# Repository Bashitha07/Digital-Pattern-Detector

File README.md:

# Digital Pattern Detector (`0011`)

**IE3004 – Digital Systems Design Assignment**  
**Sri Lanka Institute of Information Technology (SLIIT)**  
**B.Sc. (Hons) in Computer Systems Engineering**  
**Group 02**

## Project Overview

This project presents the hardware design, simulation, and PCB layout of a synchronous digital pattern detection system built with 74HC-series CMOS logic ICs.

The system:

1. Generates a pseudo-random 4-bit sequence using a linear feedback shift register (LFSR).
2. Loads each 4-bit word into a parallel-in, serial-out (PISO) shift register.
3. Transmits the word least-significant bit first.
4. Detects the overlapping binary pattern `0011` using a four-state Mealy finite-state machine (FSM).

The design was simulated in Proteus Design Suite and captured as a two-layer, through-hole PCB in KiCad.

## System Architecture

```text
+-------------------+       P3..P0       +-------------------+       X = Q0       +-------------------+
| 4-bit LFSR        | ------------------> | 4-bit PISO       | ------------------> | Mealy FSM         |
| pseudo-random     |                     | shift register   |                     | `0011` detector  |
+-------------------+                     +-------------------+                     +-------------------+
        ^                                          ^                                      |
        |                                          |                                      v
   [SW1 seed]                                 [LOAD control]                         Z (output)
                                             Common rising-edge CLK
```

All three subsystems use the same rising-edge clock.

## 1. 4-Bit LFSR

A maximal-length 4-bit LFSR cycles through all `2^4 - 1 = 15` non-zero states before repeating. The all-zero state is excluded because it would lock the register at zero.

The active-low asynchronous initialization input, controlled by push-button `SW1` and a `10 kΩ` pull-up resistor, loads the seed word:

```text
G3 G2 G1 G0 = 0001
```

The next-state equations are:

```text
Q3+ = Q2
Q2+ = Q1
Q1+ = Q0
Q0+ = Q3 XOR Q2
```

## 2. 4-Bit PISO Shift Register

The PISO register captures the LFSR output in parallel when `LOAD = 0`. When `LOAD = 1`, it shifts one bit toward `Q0` on each rising clock edge.

For `L = LOAD`, the D-input equations are:

```text
D3 = P3 · L'
D2 = Q3 · L + P2 · L'
D1 = Q2 · L + P1 · L'
D0 = Q1 · L + P0 · L'
```

The serial output is:

```text
X = Q0
```

Because transmission is least-significant bit first, a parallel word of `1100` produces the serial sequence:

```text
0 → 0 → 1 → 1
```

This sequence is the target pattern detected by the FSM.

## 3. Overlapping Mealy FSM Detector

The detector identifies `0011` using a four-state overlapping Mealy FSM. A Mealy machine generates its output from both the current state and the current input, allowing the detection pulse to occur during the clock cycle in which the final `1` arrives.

### State Encoding

| State | Encoding | Meaning |
| :--- | :---: | :--- |
| A | `00` | No useful prefix matched |
| B | `01` | Prefix `0` matched |
| C | `11` | Prefix `00` matched |
| D | `10` | Prefix `001` matched |

### Excitation and Output Equations

```text
D1 = Q0 · X' + Q1 · Q0
D0 = X'
Z  = Q1 · Q0' · X
```

The output `Z` is HIGH when the FSM is in state D and the current serial input `X` is `1`, indicating that `0011` has been detected.

### Self-Synchronization

Two consecutive `1` inputs drive the FSM to state A (`00`) from any state. This provides a practical way to place the detector in a known state without a dedicated FSM reset line.

## Integrated Circuit Allocation

| IC | Function | Packages Used | Utilization |
| :--- | :--- | :---: | :--- |
| `74HC74` | Dual D-type positive-edge flip-flop | 5 | 10 of 10 flip-flops |
| `74HC08` | Quad 2-input AND gate | 3 | 11 of 12 gates |
| `74HC32` | Quad 2-input OR gate | 1 | 4 of 4 gates |
| `74HC04` | Hex inverter | 1 | 3 of 6 inverters |
| `74HC86` | Quad 2-input XOR gate | 1 | 1 of 4 gates |

### Additional Components

- `1 × 10 kΩ` pull-up resistor
- `9 × 330 Ω` LED current-limiting resistors
- `9 ×` indicator LEDs (`D1–D9`)
- `1 ×` tactile push-button (`SW1`)
- `2 ×` 2-pin header connectors (`J1`, `J2`)

## Repository Contents

| Directory/File | Description |
| :--- | :--- |
| [`KiCad Files/`](KiCad%20Files/) | KiCad schematic, PCB layout, and project design files |
| [`Proteus/`](Proteus/) | Proteus simulation project and generated simulation files |
| [`Photos/`](Photos/) | PCB renders, board-layer views, schematics, and waveform captures |
| [`Report/`](Report/) | Technical reports and assignment documentation |
| [`README.md`](README.md) | Project overview and design documentation |

## Testing and Verification

### T1 – Seed Initialization

Stop the clock, press and release `SW1`, and verify that the LFSR is initialized to `0001`.

### T2 – LFSR Period

Apply 15 clock pulses and verify that all 15 non-zero states occur before the sequence returns to `0001`.

### T5 – FSM Synchronization

Apply two consecutive serial `1` inputs and verify that the FSM reaches state A (`00`).

### T6/T7 – Pattern Detection

1. Set `LOAD = 0` and apply one rising clock edge to load the selected LFSR word into the PISO register.
2. Set `LOAD = 1` and apply four rising clock edges.
3. For the loaded word `1100`, verify the serial sequence `0 → 0 → 1 → 1`.
4. Verify that `Z` pulses HIGH during the fourth transmitted bit, when the FSM detects the complete `0011` pattern.

## Design Files

- **KiCad:** [`KiCad Files/KiCad_Y3S1.kicad_sch`](KiCad%20Files/KiCad_Y3S1.kicad_sch) and [`KiCad Files/KiCad_Y3S1.kicad_pcb`](KiCad%20Files/KiCad_Y3S1.kicad_pcb)
- **Proteus:** [`Proteus/DSD_Final_Schematic.pdsprj`](Proteus/DSD_Final_Schematic.pdsprj)
- **Reports:** [`Report/`](Report/)

## Group Members

| Student ID | Name |
| :--- | :--- |
| `IT24103485` | Sellapperuma B.A. |
| `IT24100888` | L P Jayasinghe |
| `IT24610799` | Kalpage M.L.P. |

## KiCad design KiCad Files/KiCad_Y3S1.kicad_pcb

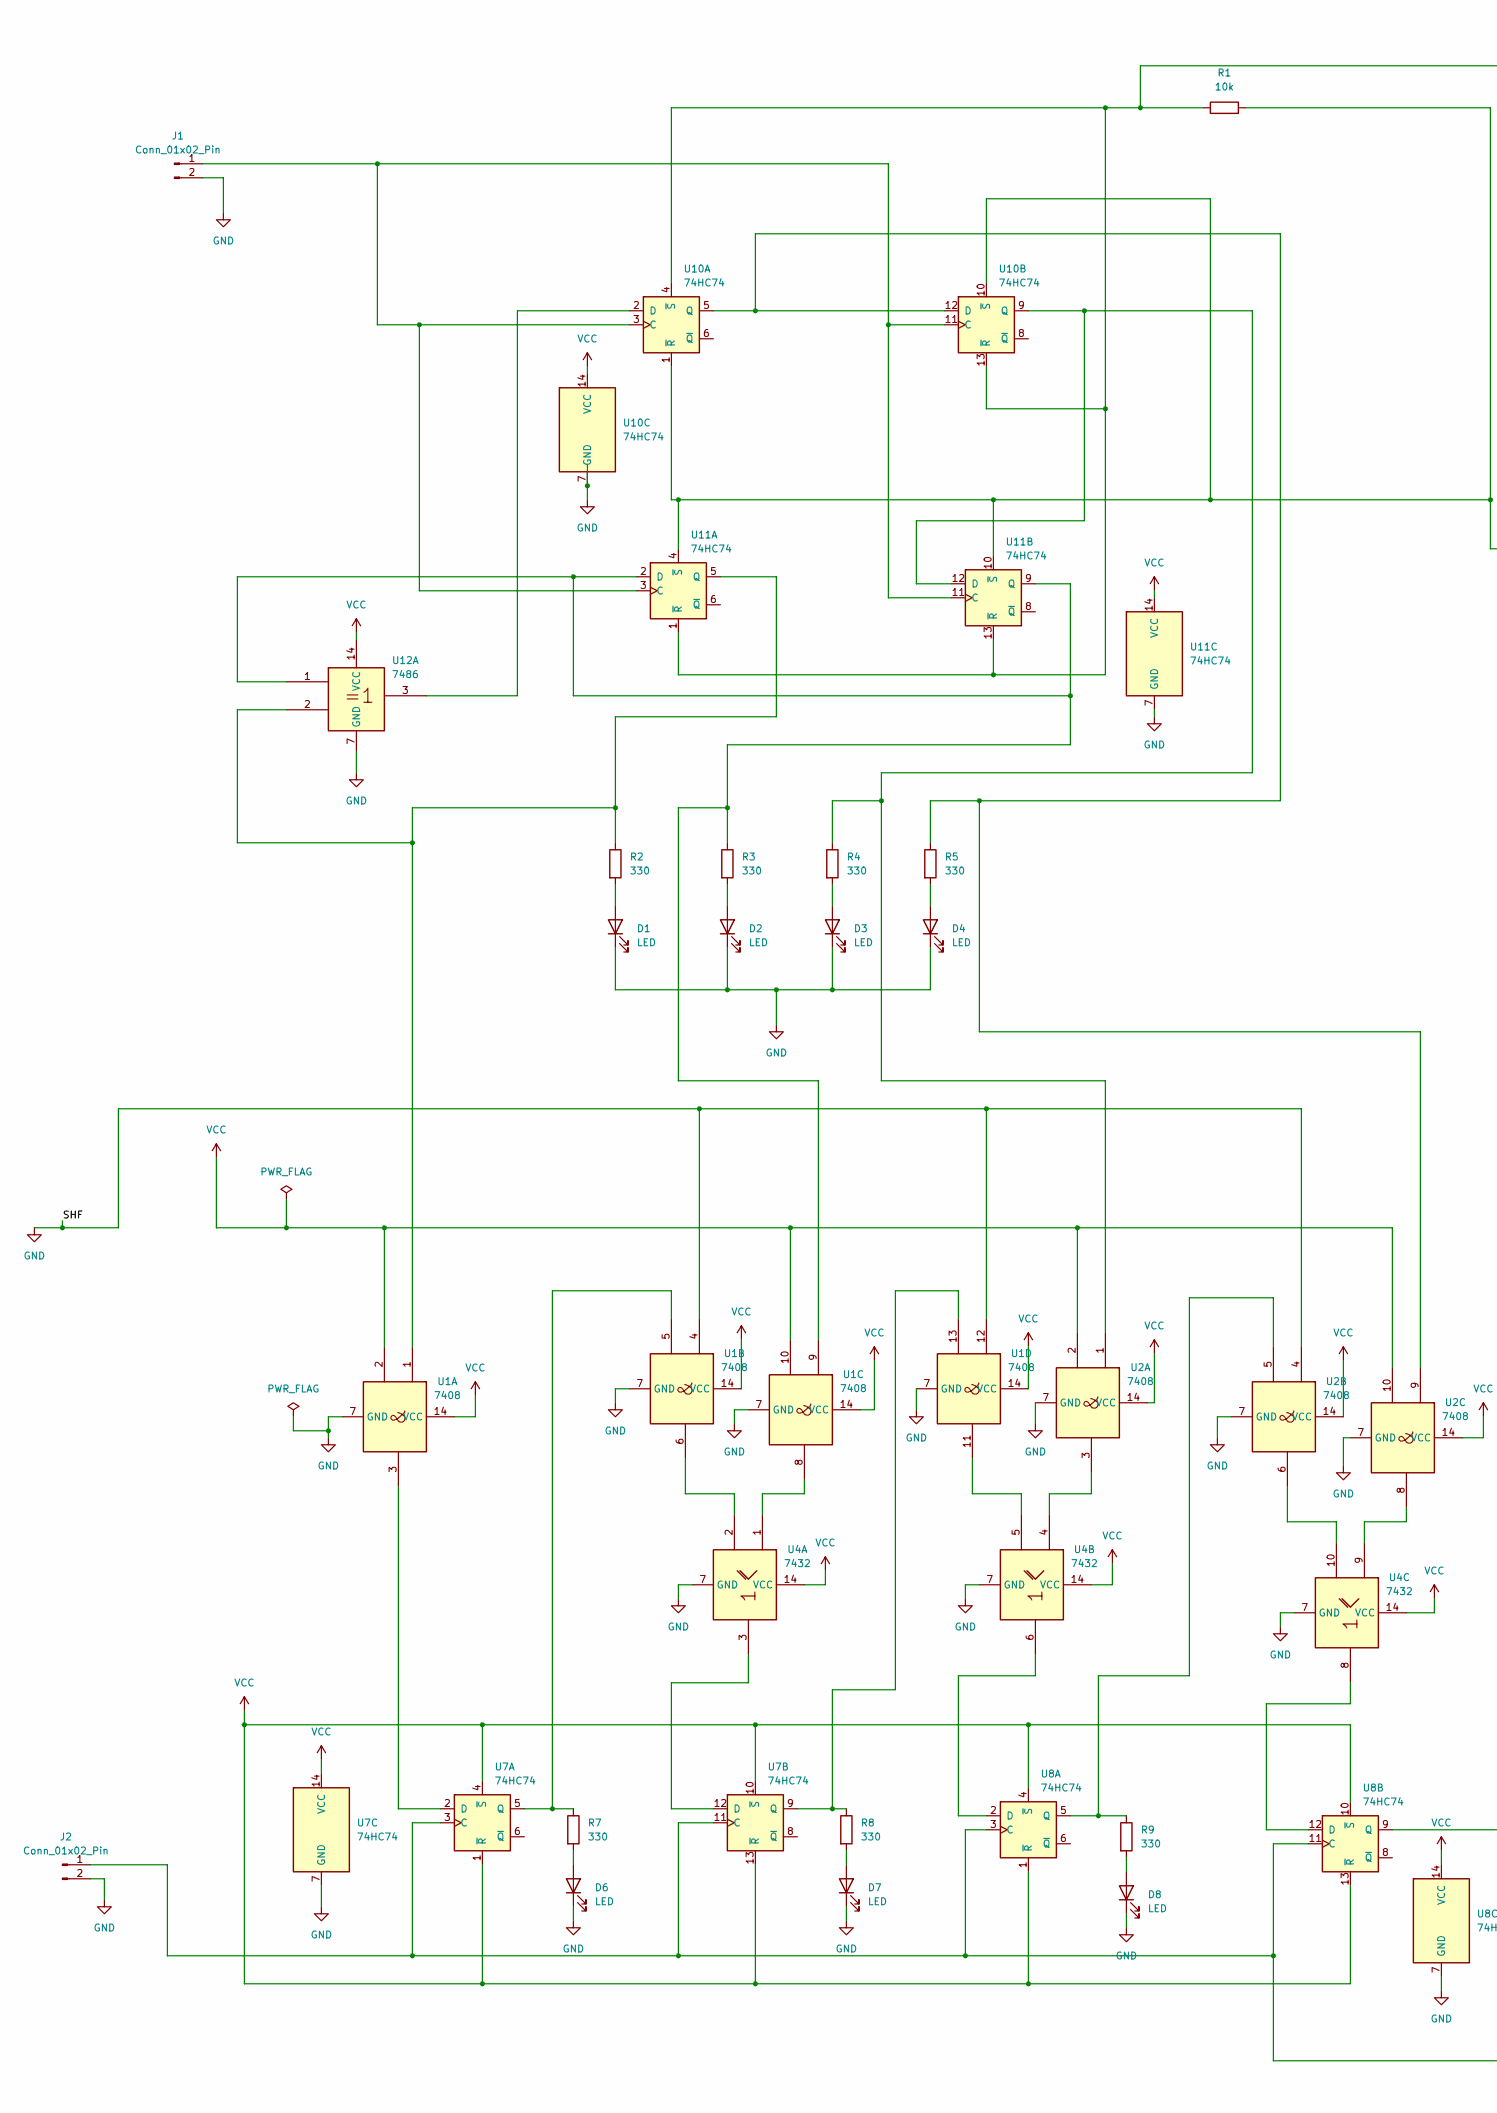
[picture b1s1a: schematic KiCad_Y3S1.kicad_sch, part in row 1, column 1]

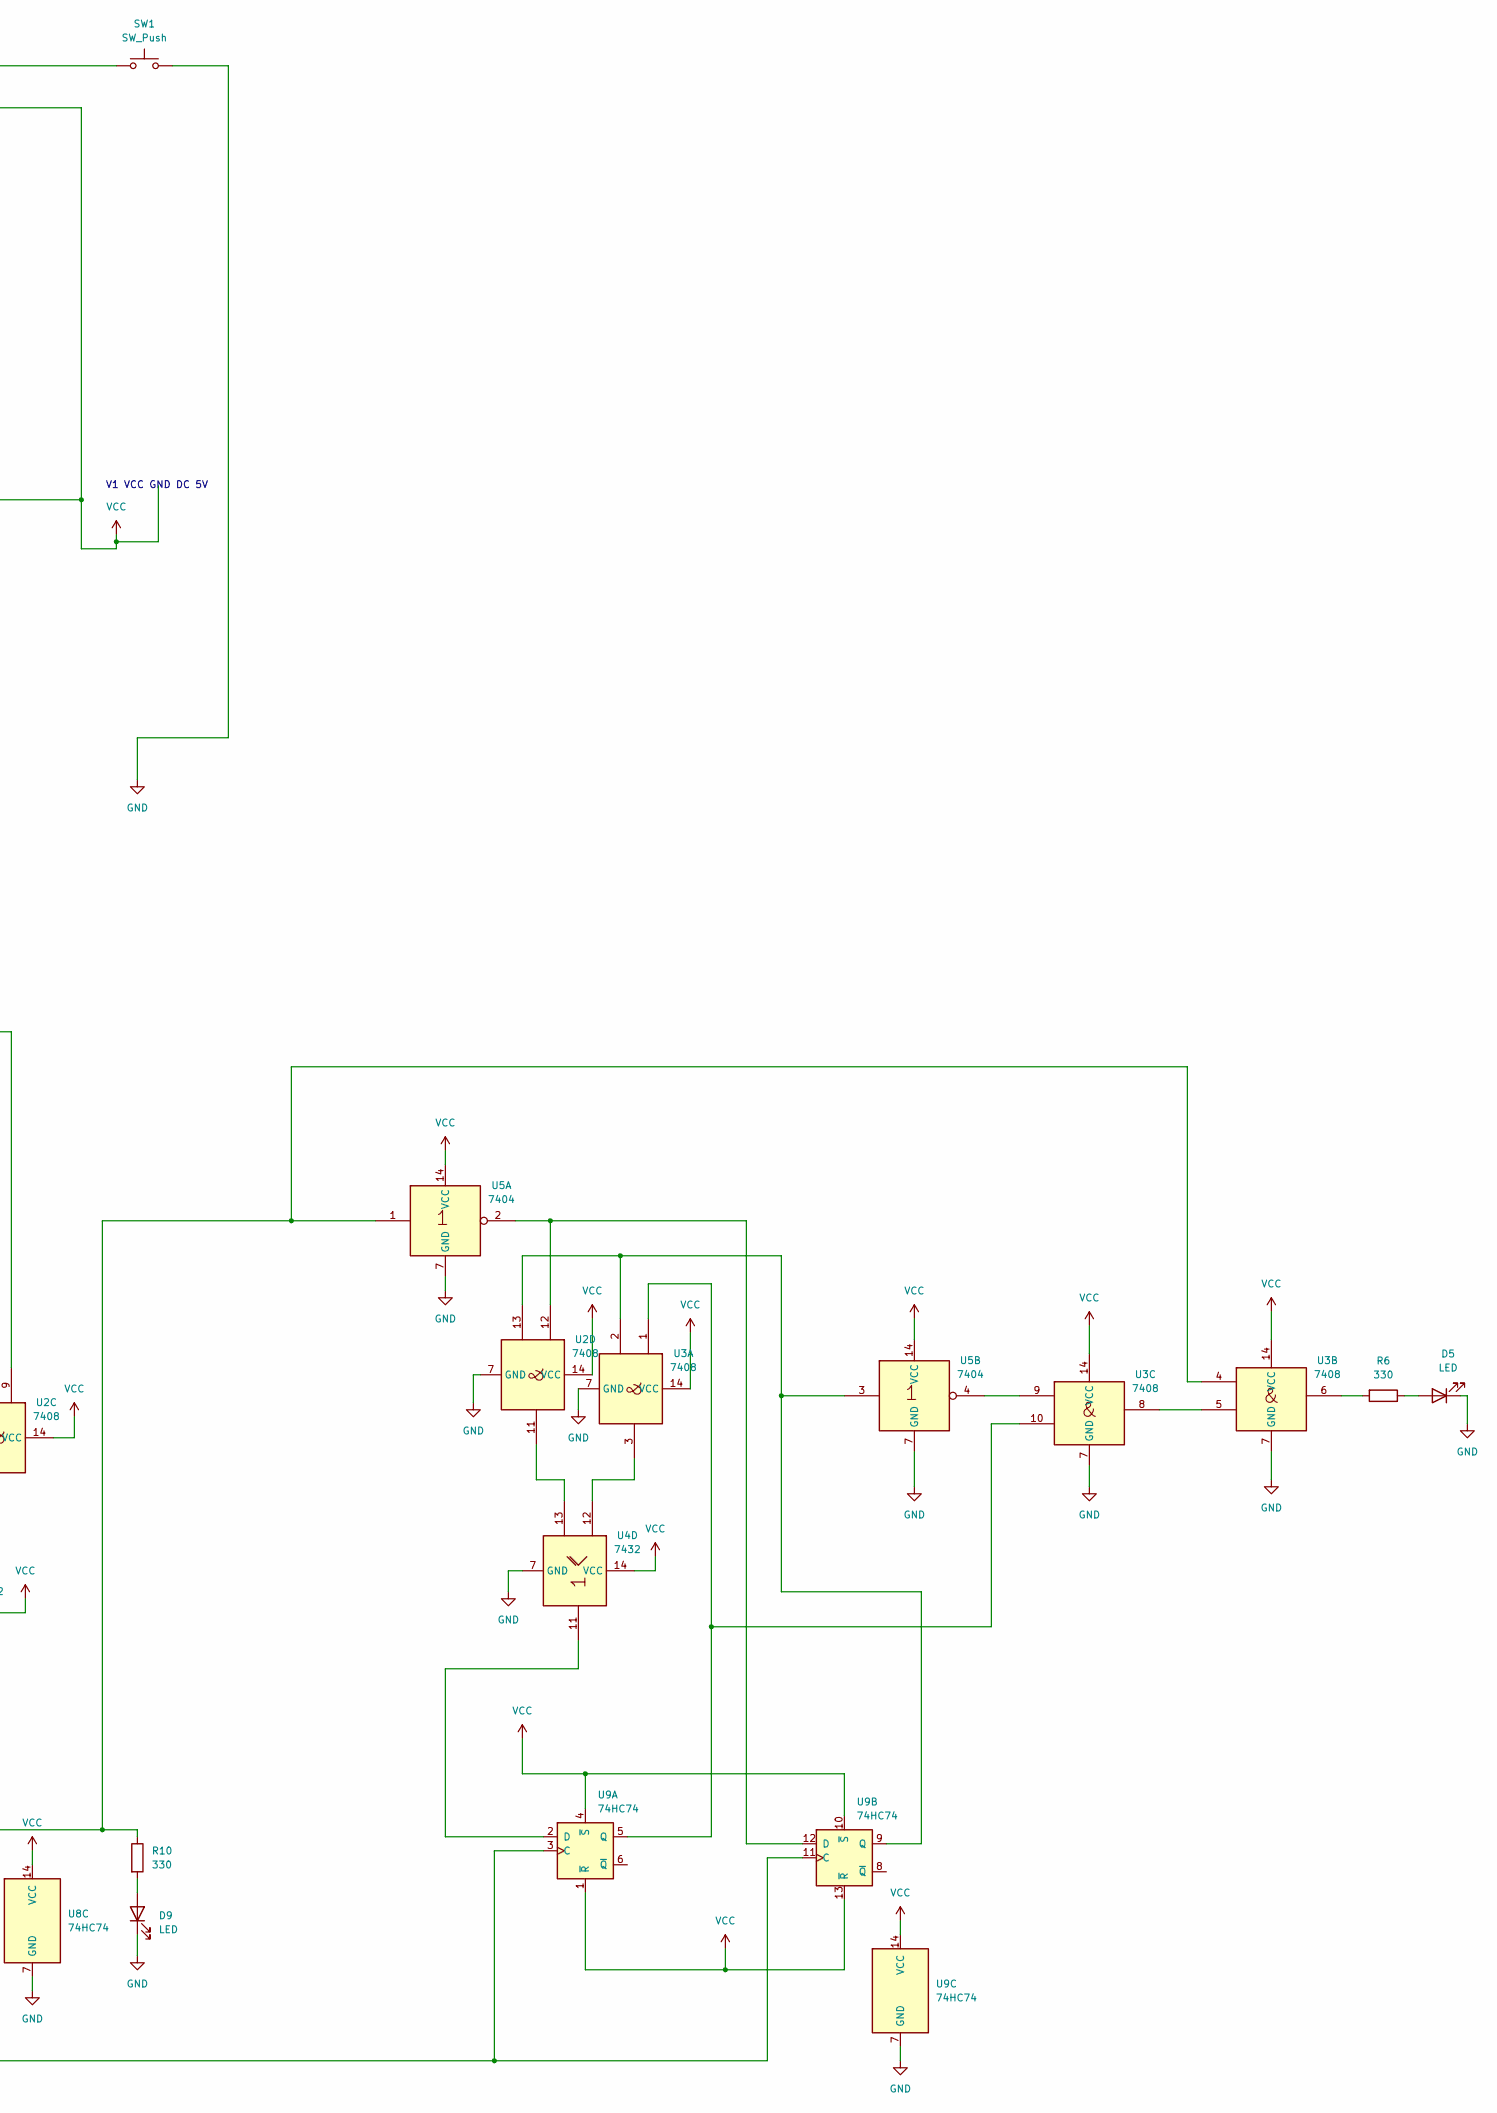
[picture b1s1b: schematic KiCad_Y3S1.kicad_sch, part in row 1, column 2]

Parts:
D1, D2, D3, D4, D5, D6, D7, D8, D9: LED; LED_D5.0mm
J1, J2: Conn_01x02_Pin; PinHeader_1x02_P2.54mm_Vertical
R1: 10k; R_Axial_DIN0207_L6.3mm_D2.5mm_P10.16mm_Horizontal
R2, R3, R4, R5, R6, R7, R8, R9, R10: 330; R_Axial_DIN0207_L6.3mm_D2.5mm_P10.16mm_Horizontal
SW1: SW_Push; SW_PUSH_6mm
U1, U2, U3: 7408; DIP-14_W7.62mm
U4: 7432; DIP-14_W7.62mm
U5: 7404; DIP-14_W7.62mm
U7, U8, U9, U10, U11: 74HC74; DIP-14_W7.62mm
U12: 7486; DIP-14_W7.62mm

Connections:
GND: D1.1 (K), D2.1 (K), D3.1 (K), D4.1 (K), D5.1 (K), D6.1 (K), D7.1 (K), D8.1 (K), D9.1 (K), J1.2, J2.2, SW1.2, U1.4, U1.7 (GND), U1.12, U2.4, U2.7 (GND), U3.7 (GND), U4.7 (GND), U5.7 (GND), U7.7 (GND), U8.7 (GND), U9.7 (GND), U10.7 (GND), U11.7 (GND), U12.7 (GND)
unnamed: D1.2 (A), R2.2
unnamed: D2.2 (A), R3.2
unnamed: D3.2 (A), R4.2
unnamed: D4.2 (A), R5.2
unnamed: D5.2 (A), R6.1
unnamed: D6.2 (A), R7.2
unnamed: D7.2 (A), R8.2
unnamed: D8.2 (A), R9.2
unnamed: D9.2 (A), R10.2
unnamed: J1.1, U10.3 (C), U10.11 (C), U11.3 (C), U11.11 (C)
unnamed: J2.1, U7.3 (C), U7.11 (C), U8.3 (C), U8.11 (C), U9.3 (C), U9.11 (C)
unnamed: R6.2, U3.6
unnamed: U1.6, U4.2
unnamed: U1.8, U4.1
unnamed: U1.11, U4.5
unnamed: U2.3, U4.4
unnamed: U2.6, U4.10
unnamed: U2.8, U4.9
unnamed: U2.11, U4.13
unnamed: U3.3, U4.12
unnamed: U3.5, U3.8
unnamed: U3.9, U5.4
unnamed: U1.3, U7.2 (D)
unnamed: R7.1, U1.5, U7.5 (Q)
unnamed: U4.3, U7.12 (D)
unnamed: R8.1, U1.13, U7.9 (Q)
unnamed: U4.6, U8.2 (D)
unnamed: R9.1, U2.5, U8.5 (Q)
unnamed: U4.8, U8.12 (D)
unnamed: R10.1, U3.4, U5.1, U8.9 (Q)
unnamed: U4.11, U9.2 (D)
unnamed: U3.1, U3.10, U9.5 (Q)
unnamed: U2.12, U5.2, U9.12 (D)
unnamed: U2.13, U3.2, U5.3, U9.9 (Q)
unnamed: U10.2 (D), U12.3
unnamed: R5.1, U2.9, U10.5 (Q), U10.12 (D)
unnamed: R1.1, SW1.1, U10.4 (~S), U10.13 (~R), U11.1 (~R), U11.13 (~R)
unnamed: R4.1, U2.1, U10.9 (Q), U11.12 (D)
unnamed: R3.1, U1.9, U11.2 (D), U11.9 (Q), U12.1
unnamed: R2.1, U1.1, U11.5 (Q), U12.2
VCC: R1.2, U1.2, U1.10, U1.14 (VCC), U2.2, U2.10, U2.14 (VCC), U3.14 (VCC), U4.14 (VCC), U5.14 (VCC), U7.1 (~R), U7.4 (~S), U7.10 (~S), U7.13 (~R), U7.14 (VCC), U8.1 (~R), U8.4 (~S), U8.10 (~S), U8.13 (~R), U8.14 (VCC), U9.1 (~R), U9.4 (~S), U9.10 (~S), U9.13 (~R), U9.14 (VCC), U10.1 (~R), U10.10 (~S), U10.14 (VCC), U11.4 (~S), U11.10 (~S), U11.14 (VCC), U12.14 (VCC)

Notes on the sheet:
V1 VCC GND DC 5V

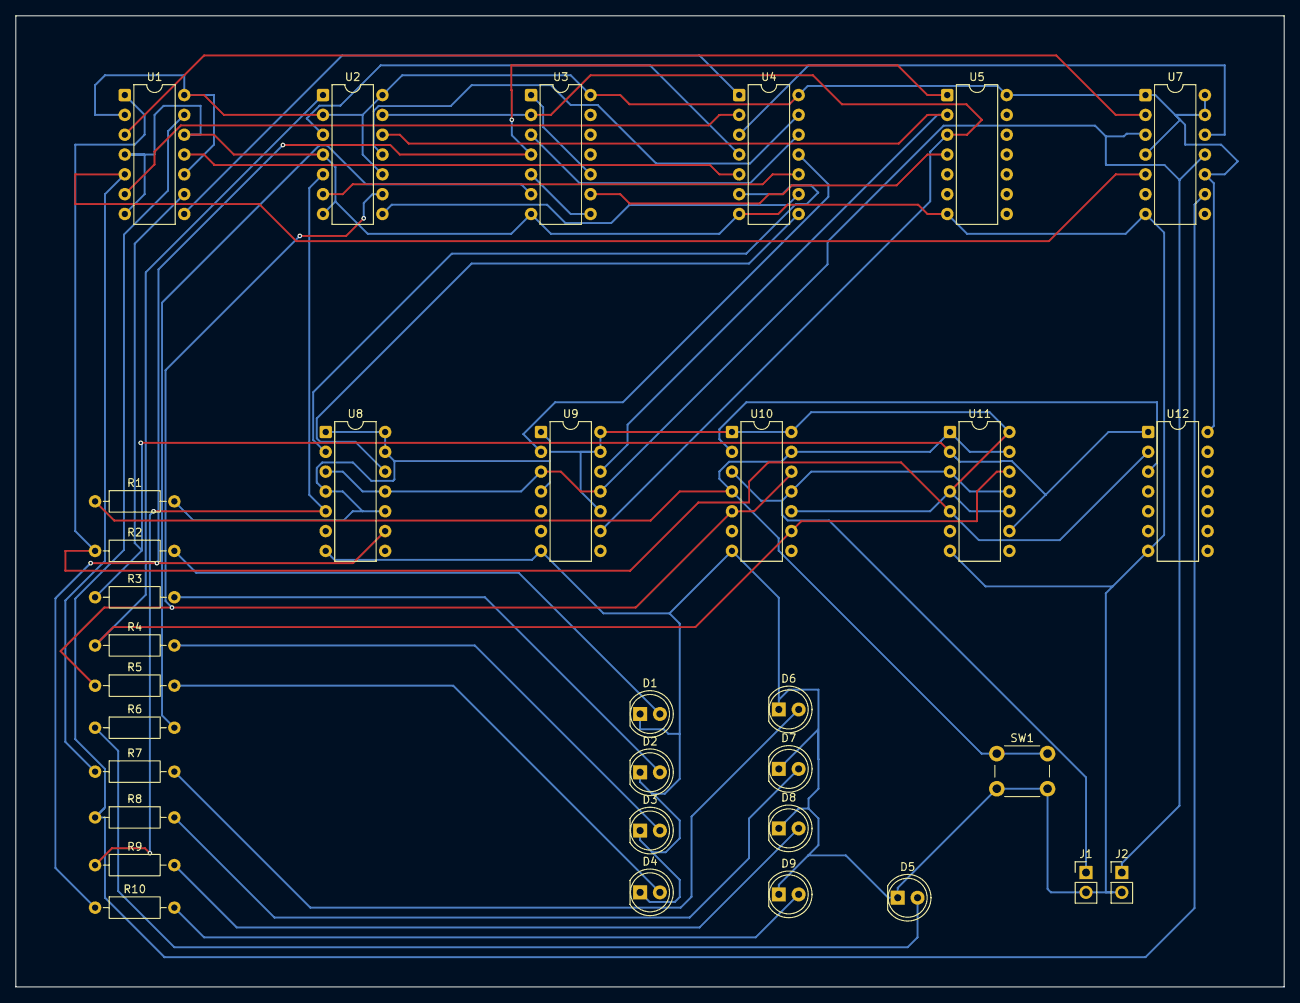
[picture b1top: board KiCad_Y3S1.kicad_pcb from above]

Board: 2 copper layers, 162.6 x 124.5 mm, 33 parts (0 on the bottom side), 42 nets.
